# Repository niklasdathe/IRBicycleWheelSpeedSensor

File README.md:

# IR Spoke Sensor

Configurable 940 nm through-beam spoke sensor for a Seeed Studio XIAO
ESP32-S3. A discrete analog front end restores a 25-50 kHz optical carrier;
ESP-IDF RMT detects its interruption and learns the wheel's spoke pattern.

This repository is the wheel-speed-sensor subsystem of
[BicycleOBU](https://github.com/niklasdathe/BicycleOBU). The
[online Interactive BOM](https://niklasdathe.github.io/IRBicycleWheelSpeedSensor/)
is generated directly from the authoritative KiCad PCB.

## Status

**Hardware V0.1 (KiCad CAD revision R4) was ordered and is preserved as a
[GitHub release](https://github.com/niklasdathe/IRBicycleWheelSpeedSensor/releases/tag/V0.1).
`main` is now hardware V0.2-dev; physical validation is still open for V0.1.**

| Area | Current evidence |
|---|---|
| Hardware | KiCad 10 ERC: 0 errors, 3 known library-sync warnings; DRC: 0 violations, 0 unconnected pads |
| Connectivity | 70 schematic endpoints, PCB pad nets and SPICE topology cross-checked |
| Simulation | Python transient, 10,000-case sweep and ngspice cross-check pass |
| Firmware | Portable core, RMT/CAN adapters and BLE CSC component implemented; ESP32-S3 target build passes, HIL pending |
| Manufacturing | Versioned JLC Gerber/BOM/CPL package generated; assembly-preview approval pending |
| Physical performance | Sunlight, alignment, contamination, vibration and power tests pending |

Do not treat simulation as production validation. The remaining gates are
listed in [TODO.md](TODO.md).

## Start here

| Goal | Guide |
|---|---|
| Understand the signal chain | [System overview](docs/system_overview.md) |
| Open the design or run the simulator | [Getting started](docs/getting_started.md) |
| Change configuration, firmware or captured CAD | [Development workflow](docs/development.md) |
| Order or review the PCB | [Manufacturing](docs/manufacturing.md) |
| Inspect or place components | [Interactive BOM](docs/interactive_bom.html) |
| Bring up and correlate a prototype | [Bring-up and test](docs/bringup.md) |
| Trace a requirement to evidence | [Verification matrix](requirements/verification_matrix.md) |
| Find a technical reference | [Documentation index](docs/README.md) |

## Hardware V0.1 at a glance

| Property | V0.1 value |
|---|---|
| Optical path | 940 nm VSMB1940X01 emitter to VEMD10940FX01 photodiode |
| Carrier | 25-50 kHz runtime range; 38 kHz default; 50% duty |
| Receiver | TLV9062 TIA/band-pass, TLV7011 Schmitt comparator |
| MCU interface | GPIO1 RMT TX, GPIO2 RMT RX with carrier demodulation |
| Wheel design range | 16-48 spokes; 60 km/h requirement, 80 km/h stress calculation |
| Receiver outline | 17.8 x 21.4 mm XIAO outline |
| Emitter outline | 21 x 15 mm, two M2.5 holes |
| Panel | Two-layer PCB with one routed mouse-bite breakaway tab |
| Remote link | 600 mm two-conductor JST-GH harness after snap-off |
| Optional interface | Official XIAO MCP2515 CAN expansion; disabled by default |
| BLE interface | Wheel-only Bluetooth Cycling Speed and Cadence Sensor (`0x1816`) |

## One-command entry points

```powershell
.\Open-IR-Spoke-Sensor.cmd
.\Open-Interactive-BOM.cmd
py -3.14 simulation\local_server.py
powershell -ExecutionPolicy Bypass -File tests\run_all.ps1
powershell -ExecutionPolicy Bypass -File hardware\export_jlc.ps1 -Revision V0.2
```

The KiCad launcher also starts the InteractiveHtmlBom watcher at
`http://127.0.0.1:8766/`; every complete PCB save regenerates and reloads the
browser view. The simulator opens at `http://127.0.0.1:8765/`. Disposable
simulation evidence is written under ignored `build/`.

## Source of truth

| Concern | Authoritative source |
|---|---|
| Tunable system values | [`config/system.json`](config/system.json) |
| Pins and electrical nets | [`hardware/connectivity.json`](hardware/connectivity.json) |
| Parts, fields and procurement | [`hardware/component_catalog.json`](hardware/component_catalog.json) |
| Captured schematic and routing | [`hardware/ir_spoke_link/layout_manifest.json`](hardware/ir_spoke_link/layout_manifest.json) |
| Requirements | [`requirements/requirements.yaml`](requirements/requirements.yaml) |
| Project paths and revision | [`project_manifest.json`](project_manifest.json) |
| Hardware/software versions | [`docs/versioning.md`](docs/versioning.md) |
| Changes between releases | [`CHANGELOG.md`](CHANGELOG.md) |

Generators restore the captured user layout and must not synthesize, remove or
reroute tracks. See [CONTRIBUTING.md](CONTRIBUTING.md) before changing CAD or
generated files.

## License

No project license has been selected yet. Until one is added, the repository
must not be presented as granting open-hardware, software or documentation
reuse rights.

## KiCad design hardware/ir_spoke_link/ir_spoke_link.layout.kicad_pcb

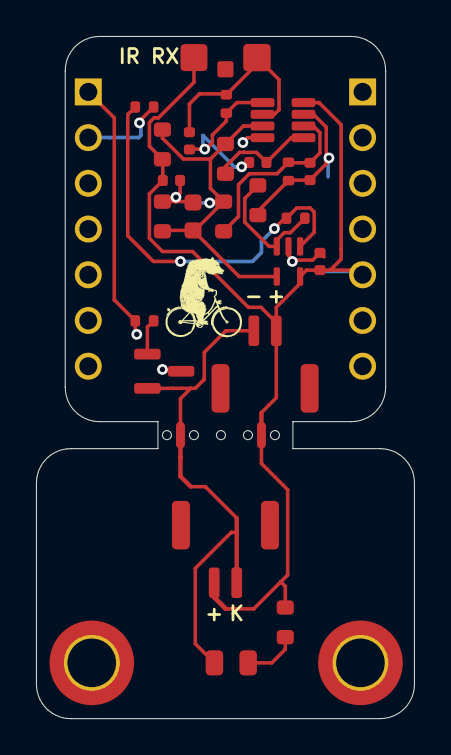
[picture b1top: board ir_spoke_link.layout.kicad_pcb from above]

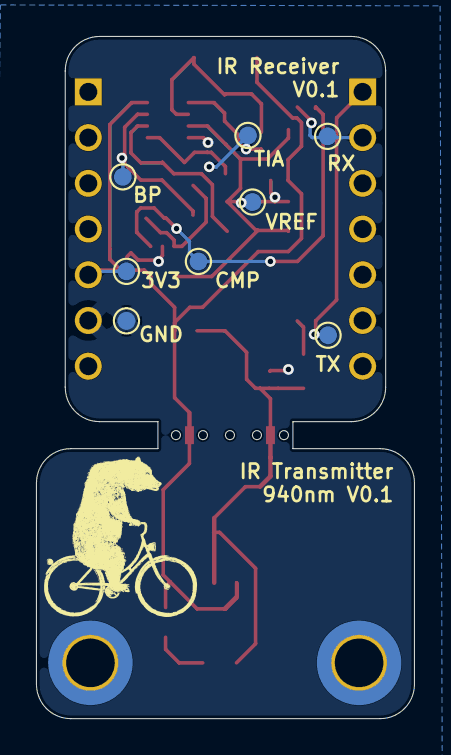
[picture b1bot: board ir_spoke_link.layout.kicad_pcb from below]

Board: 2 copper layers, 21.0 x 37.9 mm, 43 parts (8 on the bottom side), 17 nets.

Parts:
C1: 1u; C_0603_1608Metric
C2: 120p; C_0402_1005Metric
C3: 1n; C_0402_1005Metric
C4: 4.7p; C_0402_1005Metric
C5, C6: 100n; C_0402_1005Metric
D1: VSMB1940X01; LED_0805_2012Metric
D2: VEMD10940FX01; VEMD10940F_SideView
J1: XIAO_LEFT; PinSocket_1x07_P2.54mm_Vertical
J2: XIAO_RIGHT; PinSocket_1x07_P2.54mm_Vertical
J3: TX CABLE; JST_GH_SM02B-GHS-TB_1x02-1MP_P1.25mm_Horizontal
J4: JST GH LED; JST_GH_SM02B-GHS-TB_1x02-1MP_P1.25mm_Horizontal
MB1, MB2, MB3, MB4, MB5: BREAKAWAY_NPTH_0.5; Breakaway_MouseBite_0.5mm
MH1, MH2: MountingHole_2.7mm_M2.5_DIN965_Pad_TopBottom
NT1, NT2: TEMP_BREAKAWAY_LINK; NetTie-2_SMD_Pad0.5mm
Q1: S8050; SOT-23
R1: 39R; R_0603_1608Metric
R2: 1k; R_0402_1005Metric
R3, R4, R7, R9: 10k; R_0603_1608Metric
R5: 33k; R_0402_1005Metric
R6: 16k; R_0603_1608Metric
R8: 560k; R_0402_1005Metric
R10: 1M; R_0402_1005Metric
R11: 100R; R_0402_1005Metric
TP1: GND; TestPoint_Pad_D1.0mm
TP2: +3V3; TestPoint_Pad_D1.0mm
TP3: VREF; TestPoint_Pad_D1.0mm
TP4: TX_CARRIER_GPIO1; TestPoint_Pad_D1.0mm
TP5: TIA_OUT; TestPoint_Pad_D1.0mm
TP6: BANDPASS; TestPoint_Pad_D1.0mm
TP7: COMP_OUT; TestPoint_Pad_D1.0mm
TP8: RX_RMT_GPIO2; TestPoint_Pad_D1.0mm
U1: TLV9062IDDFR; SOT-23-8
U2: TLV7011DCKR; SOT-353_SC-70-5

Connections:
+3V3: C5.1, C6.1, D2.1, J2.5, J3.2, NT2.2, R3.1, TP2.1, U1.8, U2.5
+3V3_LED: J4.2, NT2.1, R1.1
BANDPASS: C4.1, R8.1, R9.1, TP6.1, U1.7
BP_IN: C3.2, R6.1, U1.5
BP_NEG: C4.2, R7.1, R8.2, U1.6
COMP_OUT: R10.1, R11.1, TP7.1, U2.1
COMP_PLUS: R9.2, R10.2, U2.3
GND: C1.2, C5.2, C6.2, J2.6, Q1.3, R4.2, TP1.1, U1.4, U2.2
LED_A: D1.2, R1.2
LED_K_REMOTE: D1.1, J4.1, NT1.1
LED_K_SWITCHED: J3.1, NT1.2, Q1.2
PD_ANODE: C2.2, D2.3, R5.2, U1.2
Q_BASE: Q1.1, R2.2
RX_RMT_GPIO2: J1.2, R11.2, TP8.1
TIA_OUT: C2.1, C3.1, R5.1, TP5.1, U1.1
TX_CARRIER_GPIO1: J1.1, R2.1, TP4.1
VREF: C1.1, R3.2, R4.1, R6.2, R7.2, TP3.1, U1.3, U2.4

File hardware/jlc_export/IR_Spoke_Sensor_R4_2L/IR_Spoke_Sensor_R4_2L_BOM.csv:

Comment,Designator,Footprint,LCSC Part #
100R,R11,R_0402_1005Metric,C25076
100n,"C5,C6",C_0402_1005Metric,C1525
10k,"R3,R4,R7,R9",R_0603_1608Metric,C25804
120p,C2,C_0402_1005Metric,C106996
16k,R6,R_0603_1608Metric,C4210
1M,R10,R_0402_1005Metric,C26083
1k,R2,R_0402_1005Metric,C11702
1n,C3,C_0402_1005Metric,C1523
1u,C1,C_0603_1608Metric,C15849
33k,R5,R_0402_1005Metric,C25779
39R,R1,R_0603_1608Metric,C23154
4.7p,C4,C_0402_1005Metric,C1569
560k,R8,R_0402_1005Metric,C132339
JST GH LED,J4,JST_GH_SM02B-GHS-TB_1x02-1MP_P1.25mm_Horizontal,C189893
S8050,Q1,SOT-23,C2146
TLV7011DCKR,U2,SOT-353_SC-70-5,C193688
TLV9062IDDFR,U1,SOT-23-8,C2867884
TX CABLE,J3,JST_GH_SM02B-GHS-TB_1x02-1MP_P1.25mm_Horizontal,C189893
VEMD10940FX01,D2,VEMD10940F_SideView,C7104273
VSMB1940X01,D1,LED_0805_2012Metric,C3151600

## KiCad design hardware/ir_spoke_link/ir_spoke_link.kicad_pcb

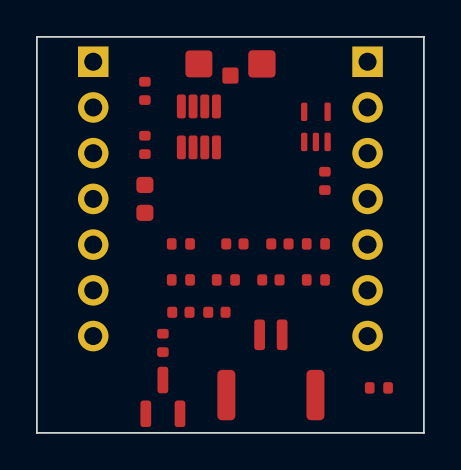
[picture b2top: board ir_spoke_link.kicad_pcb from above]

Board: 2 copper layers, 21.5 x 22.0 mm, 23 parts (0 on the bottom side), 14 nets, no tracks yet.

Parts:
C1: 1u; C_0603_1608Metric
C2: 120p; C_0402_1005Metric
C3: 1n; C_0402_1005Metric
C4: 4.7p; C_0402_1005Metric
C5, C6: 100n; C_0402_1005Metric
D2: VEMD10940FX01; VEMD10940F_SideView
J1: XIAO_LEFT; PinSocket_1x07_P2.54mm_Vertical
J2: XIAO_RIGHT; PinSocket_1x07_P2.54mm_Vertical
J3: TX CABLE; JST_GH_BM02B-GHS-TBT_1x02-1MP_P1.25mm_Vertical
Q1: S8050; SOT-23
R2: 1k; R_0402_1005Metric
R3, R4, R7, R9: 10k; R_0402_1005Metric
R5: 33k; R_0402_1005Metric
R6: 16k; R_0402_1005Metric
R8: 560k; R_0402_1005Metric
R10: 1M; R_0402_1005Metric
R11: 100R; R_0402_1005Metric
U1: TLV9062IDDFR; SOT-23-8
U2: TLV7011DCKR; SOT-353_SC-70-5

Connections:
+3V3: C5.1, C6.1, D2.1, J2.5, R3.1, U1.8, U2.5
BANDPASS: C4.1, R8.1, R9.1, U1.7
BP_IN: C3.2, R6.1, U1.5
BP_NEG: C4.2, R7.1, R8.2, U1.6
COMP_OUT: R10.1, R11.1, U2.1
COMP_PLUS: R9.2, R10.2, U2.3
GND: C1.2, C5.2, C6.2, J2.6, Q1.3, R4.2, U1.4, U2.2
LED_K_SWITCHED: J3.2, Q1.2
PD_ANODE: C2.2, D2.3, R5.2, U1.2
Q_BASE: Q1.1, R2.2
RX_RMT_GPIO2: J1.2, R11.2
TIA_OUT: C2.1, C3.1, R5.1, U1.1
TX_CARRIER_GPIO1: J1.1, R2.1
VREF: C1.1, R3.2, R4.1, R6.2, R7.2, U1.3, U2.4

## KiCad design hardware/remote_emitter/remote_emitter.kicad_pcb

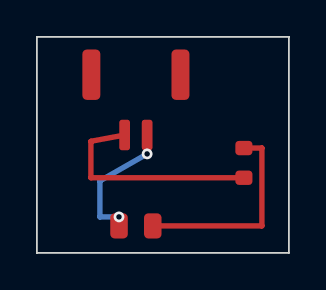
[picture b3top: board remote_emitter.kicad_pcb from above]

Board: 2 copper layers, 14.0 x 12.0 mm, 3 parts (0 on the bottom side), 3 nets.

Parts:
D1: VSMB1940X01; LED_0805_2012Metric
J4: JST GH LED; JST_GH_BM02B-GHS-TBT_1x02-1MP_P1.25mm_Vertical
R1: 39R; R_0603_1608Metric

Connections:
+3V3_LED: J4.1, R1.1
LED_A: D1.2, R1.2
LED_K_SWITCHED: D1.1, J4.2

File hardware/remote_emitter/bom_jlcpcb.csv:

Comment,Designator,Footprint,Manufacturer Part Number,LCSC Part Number,JLCPCB Library,Stock checked 2026-07-27,Notes
940nm side-view IR LED,D1,LED_0805_2012Metric,VSMB1940X01,C3151600,Extended,Verify before order,45.4mA calculated
39R 1% 0.1W,R1,R_0603_1608Metric,0603WAF390JT5E,C23154,Basic,In stock,LED current limit
JST GH secure-lock header,J4,JST_GH_BM02B-GHS-TBT_1x02-1MP_P1.25mm_Vertical,BM02B-GHS-TBT(LF)(SN),C161690,Extended,1082,1A 50V secure lock
